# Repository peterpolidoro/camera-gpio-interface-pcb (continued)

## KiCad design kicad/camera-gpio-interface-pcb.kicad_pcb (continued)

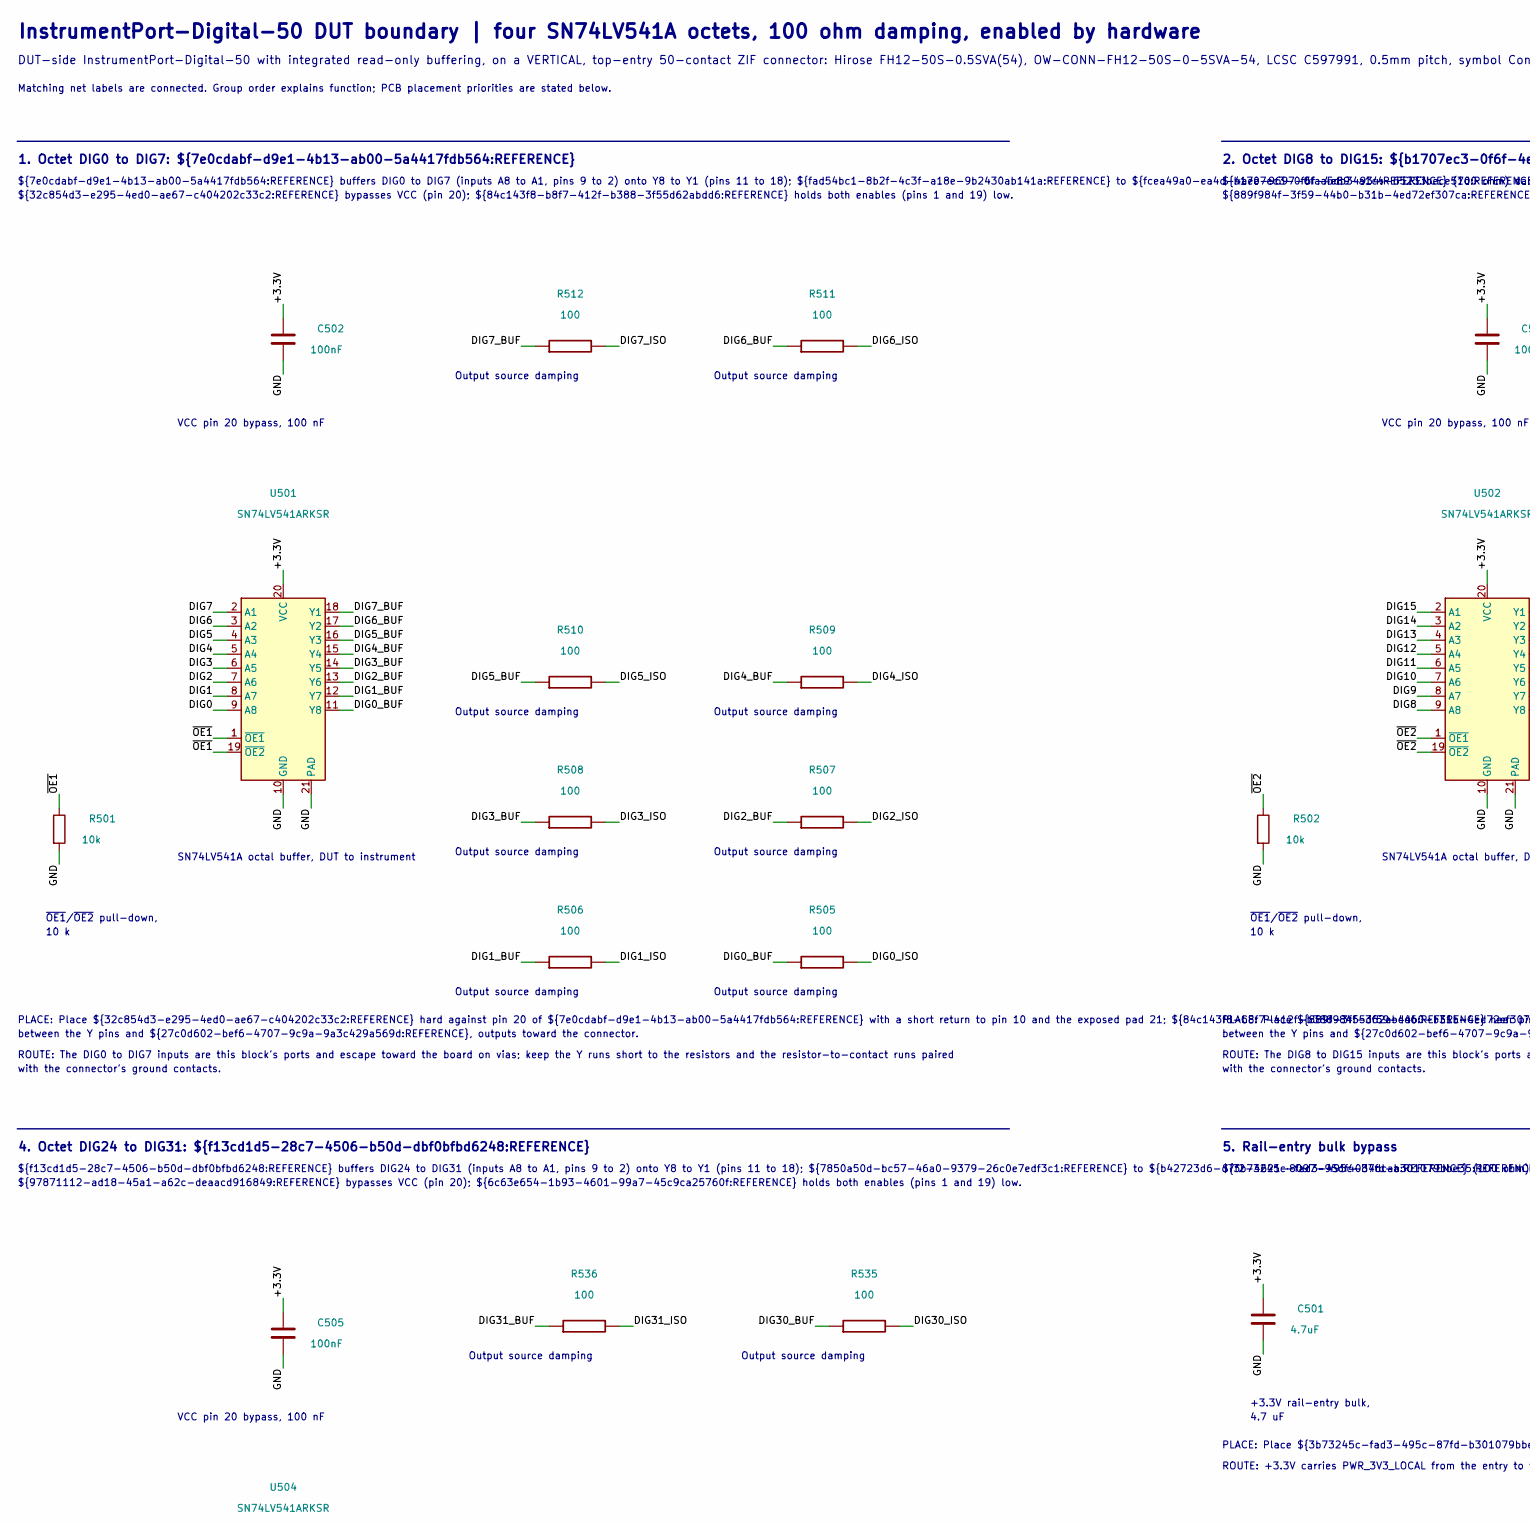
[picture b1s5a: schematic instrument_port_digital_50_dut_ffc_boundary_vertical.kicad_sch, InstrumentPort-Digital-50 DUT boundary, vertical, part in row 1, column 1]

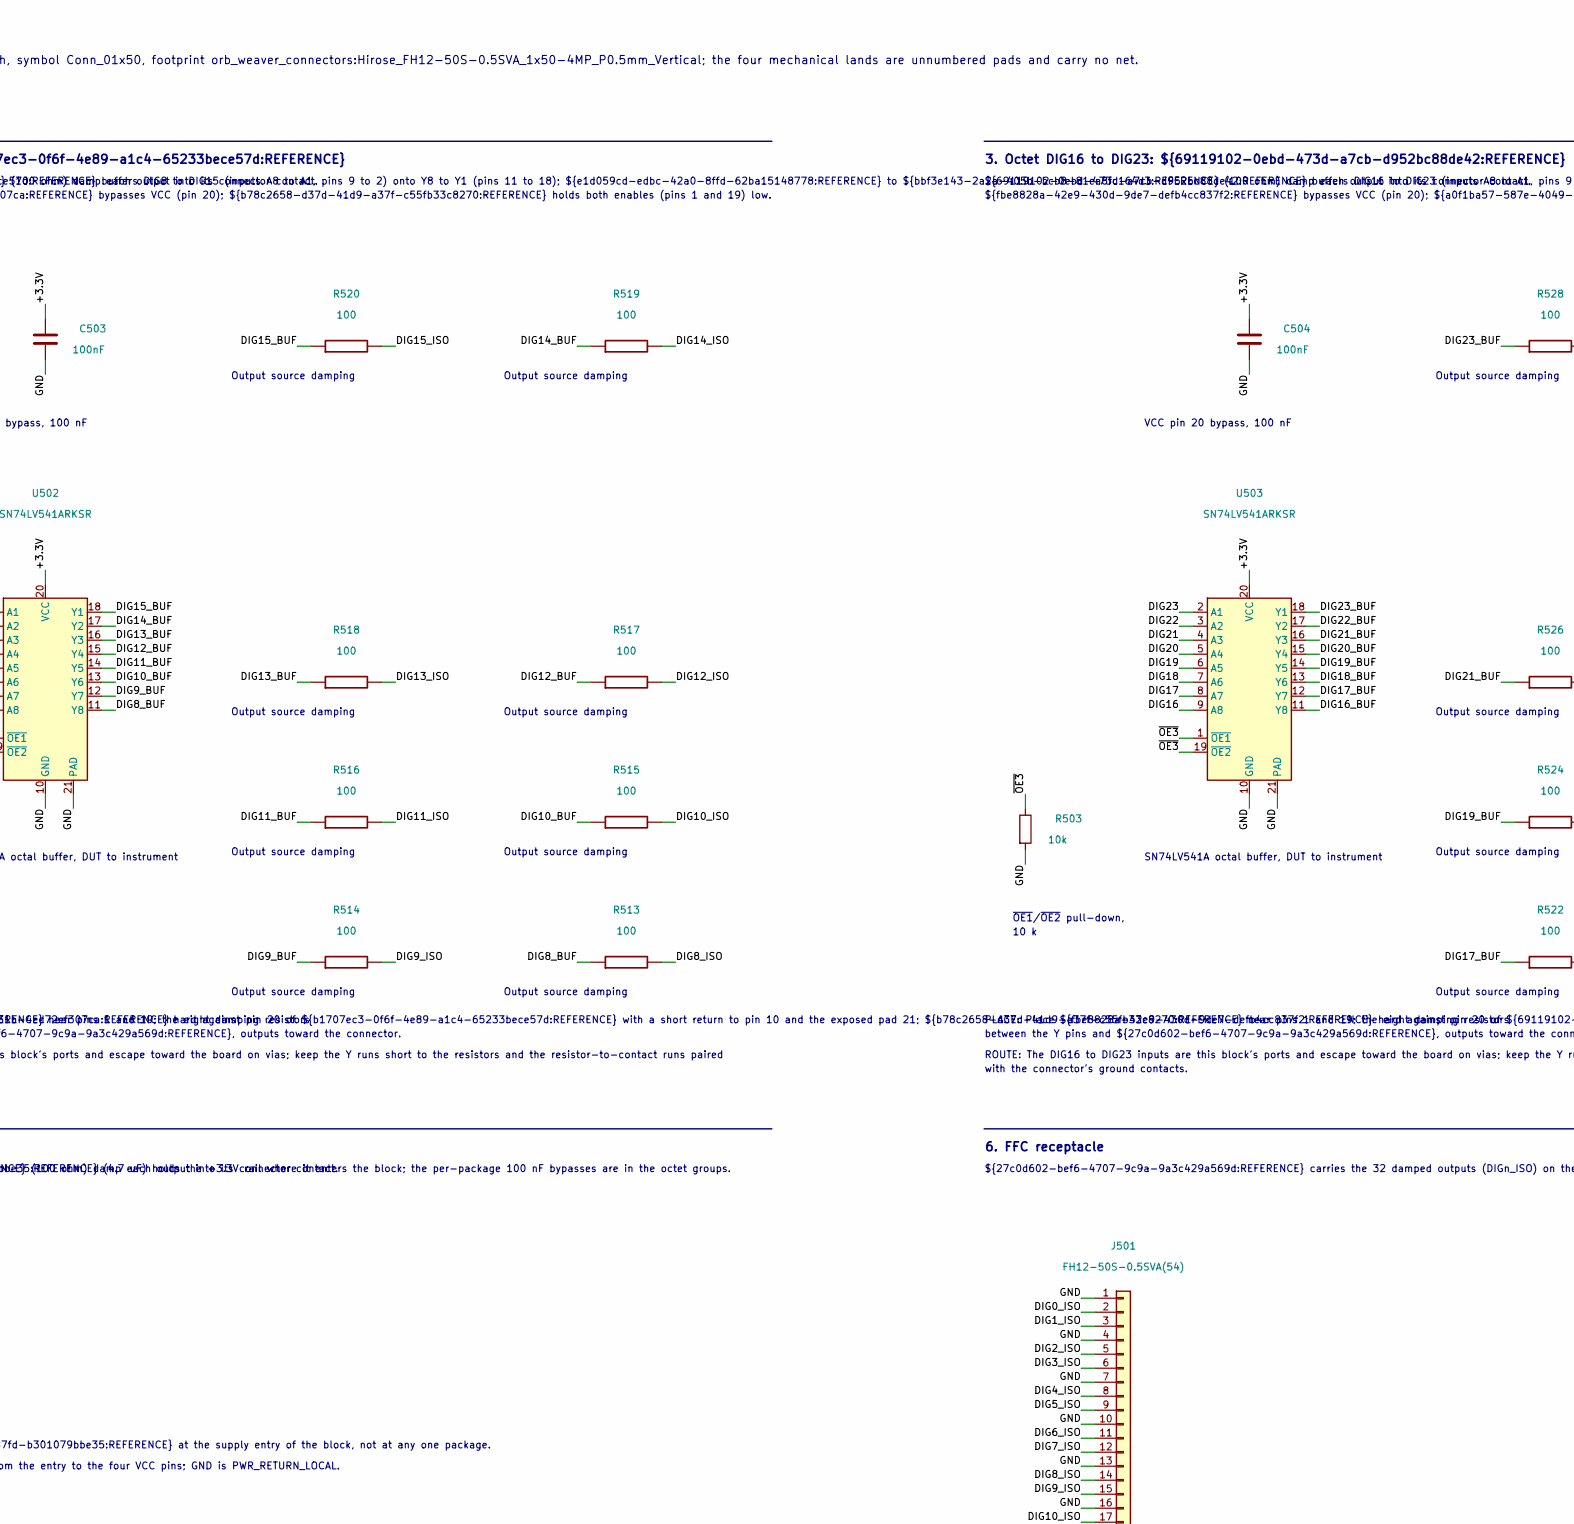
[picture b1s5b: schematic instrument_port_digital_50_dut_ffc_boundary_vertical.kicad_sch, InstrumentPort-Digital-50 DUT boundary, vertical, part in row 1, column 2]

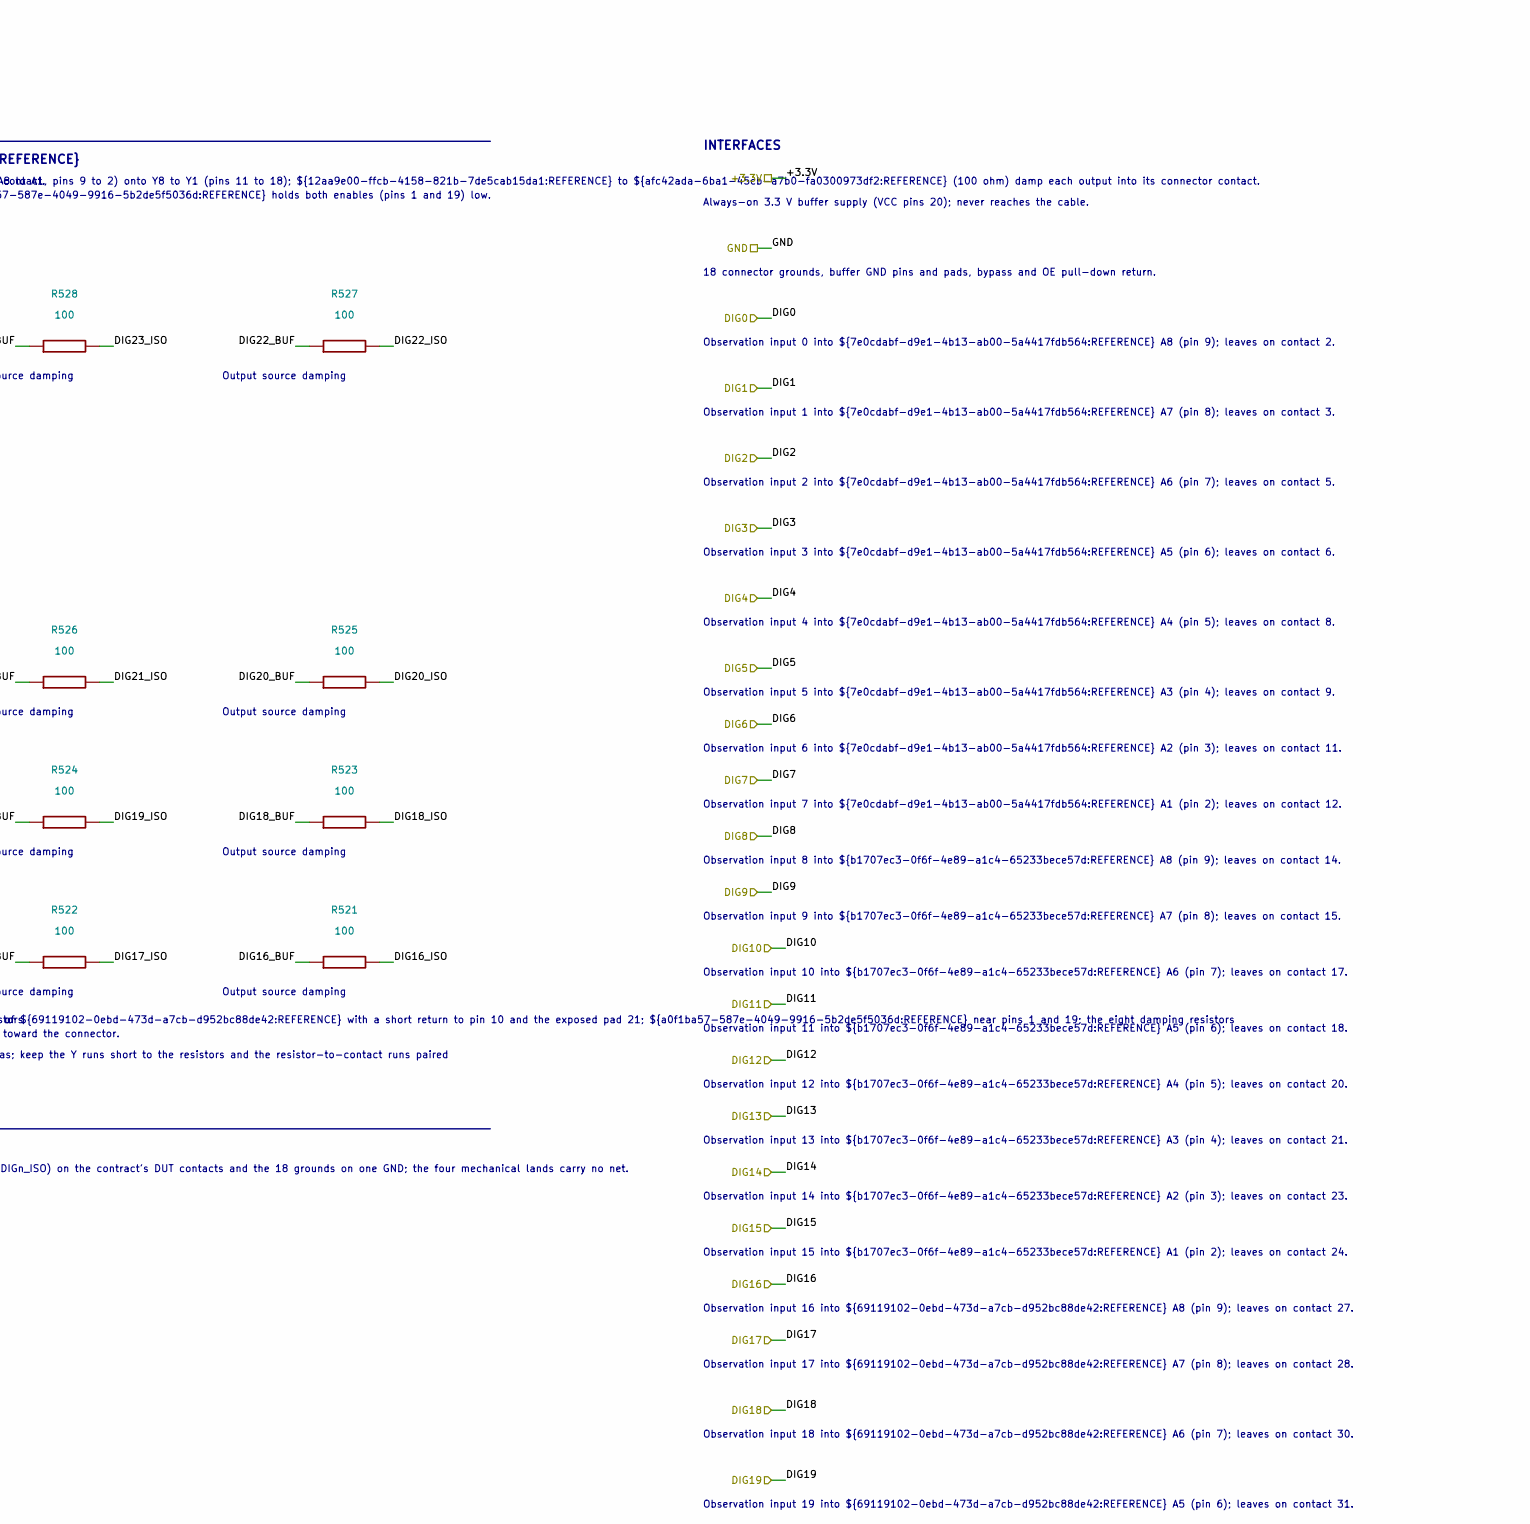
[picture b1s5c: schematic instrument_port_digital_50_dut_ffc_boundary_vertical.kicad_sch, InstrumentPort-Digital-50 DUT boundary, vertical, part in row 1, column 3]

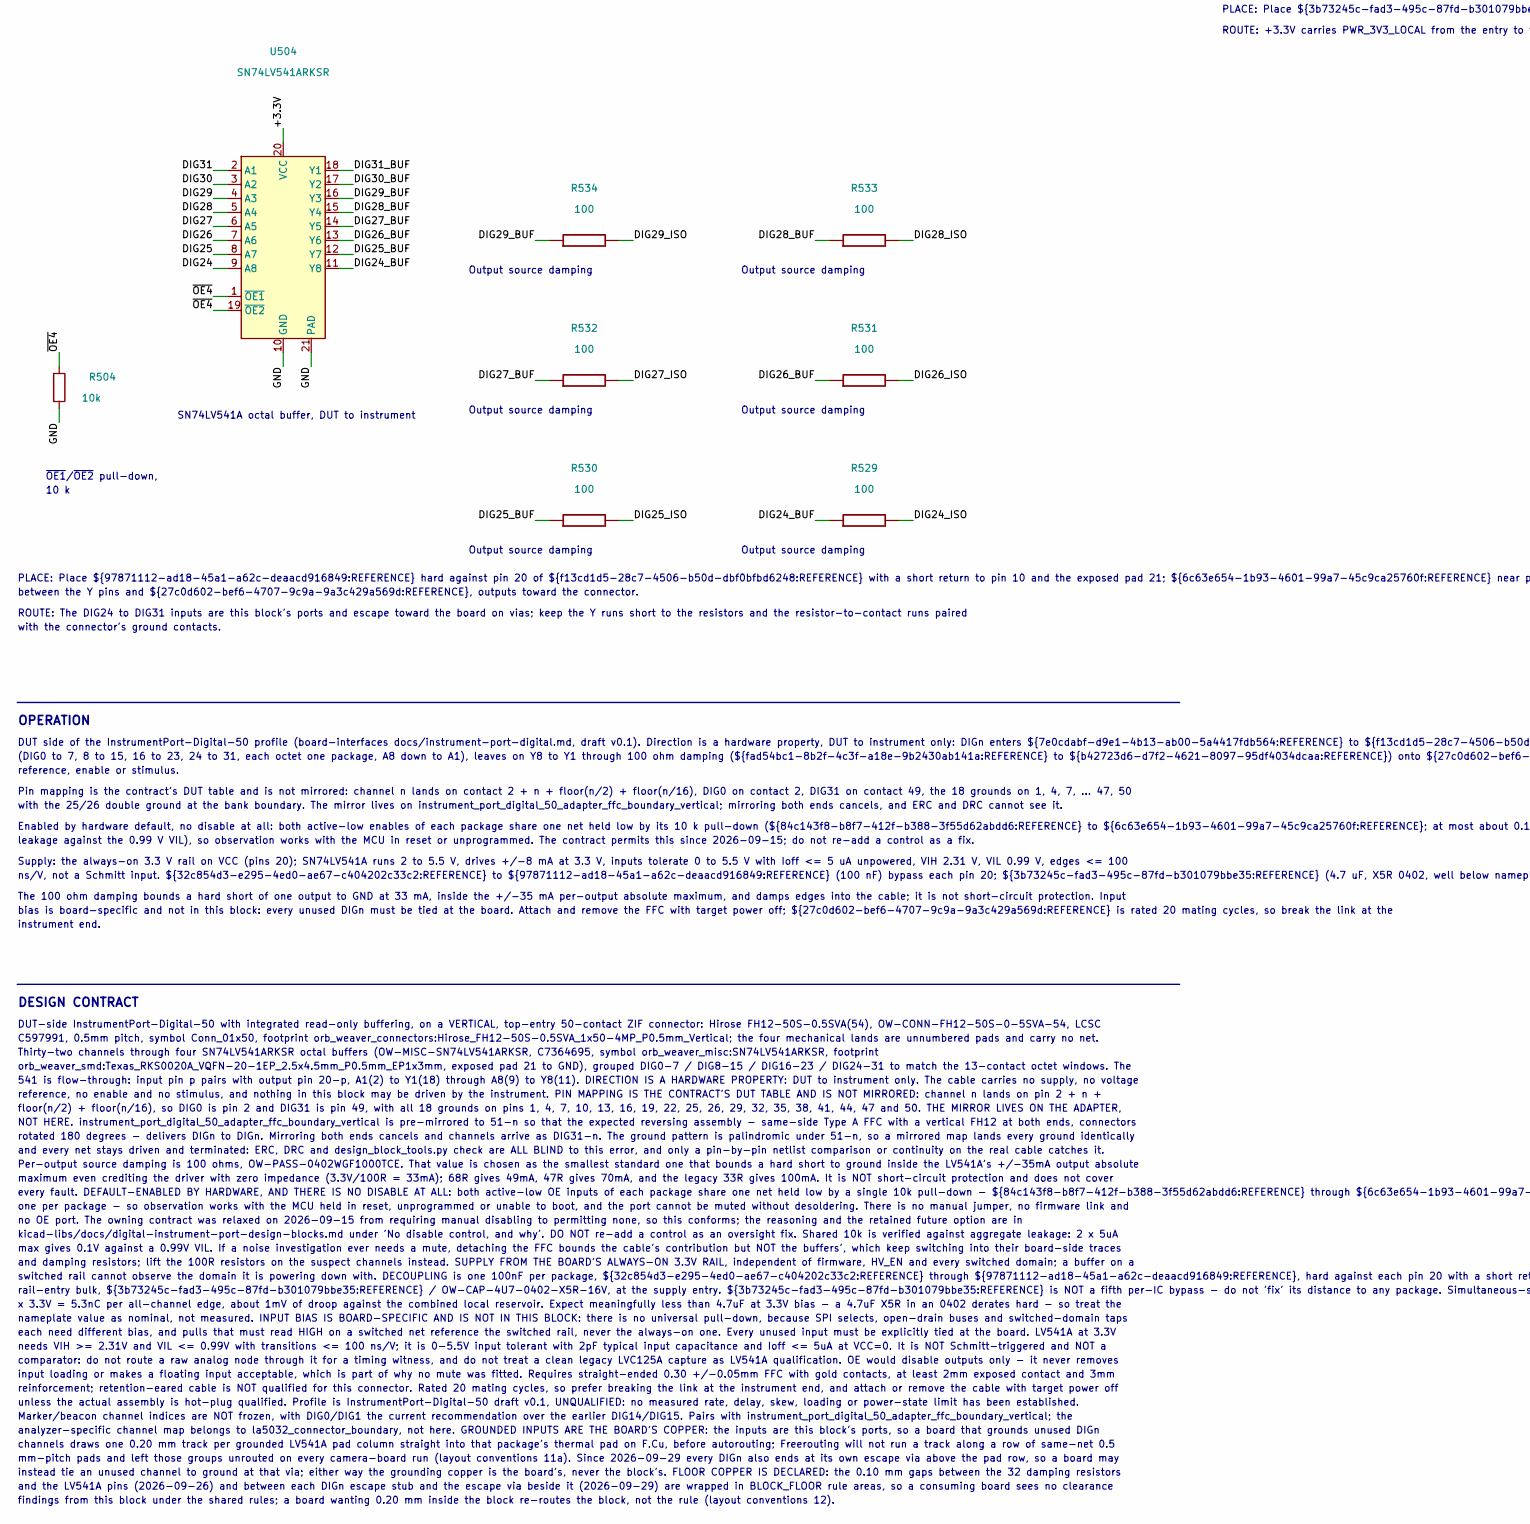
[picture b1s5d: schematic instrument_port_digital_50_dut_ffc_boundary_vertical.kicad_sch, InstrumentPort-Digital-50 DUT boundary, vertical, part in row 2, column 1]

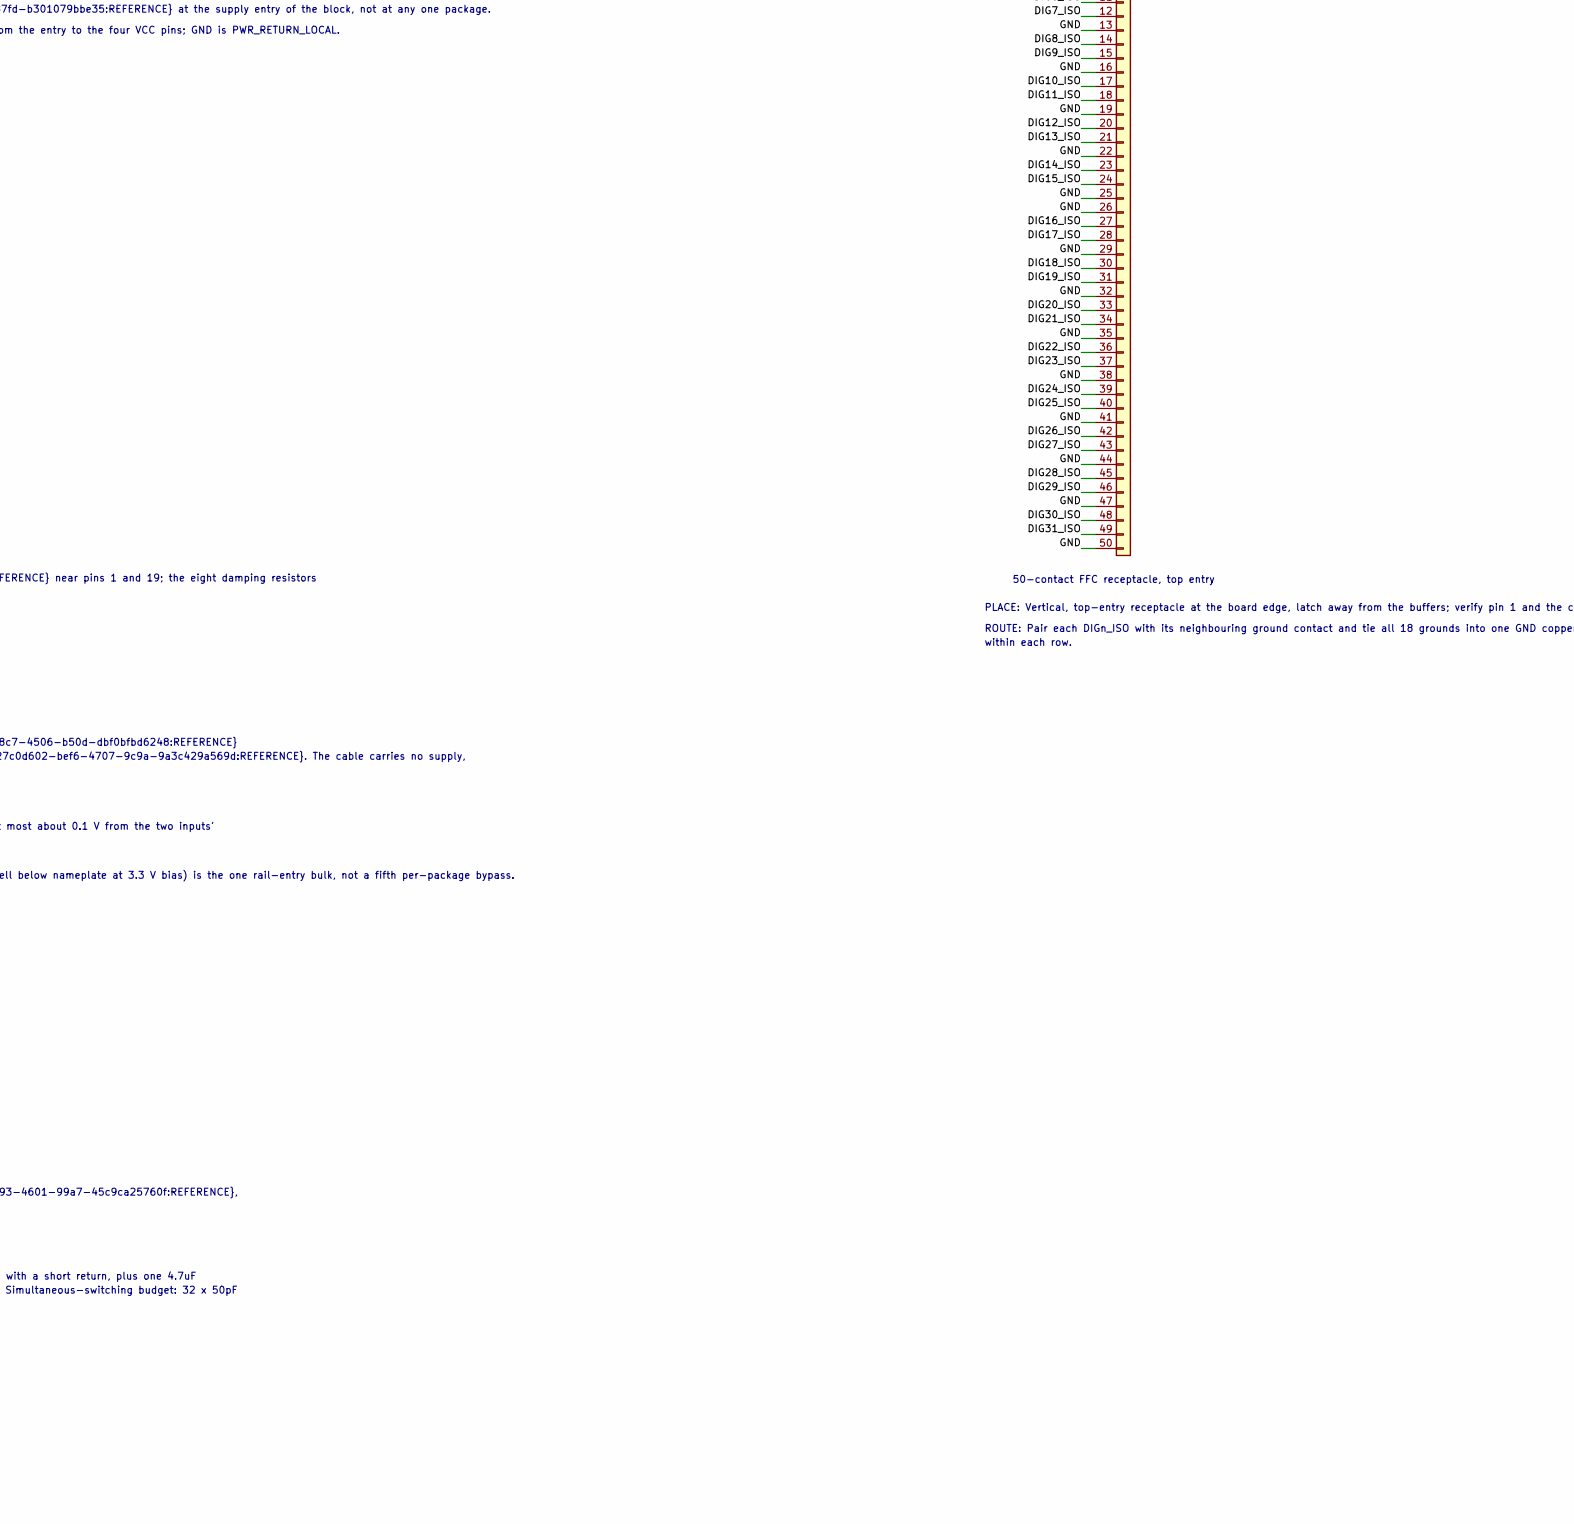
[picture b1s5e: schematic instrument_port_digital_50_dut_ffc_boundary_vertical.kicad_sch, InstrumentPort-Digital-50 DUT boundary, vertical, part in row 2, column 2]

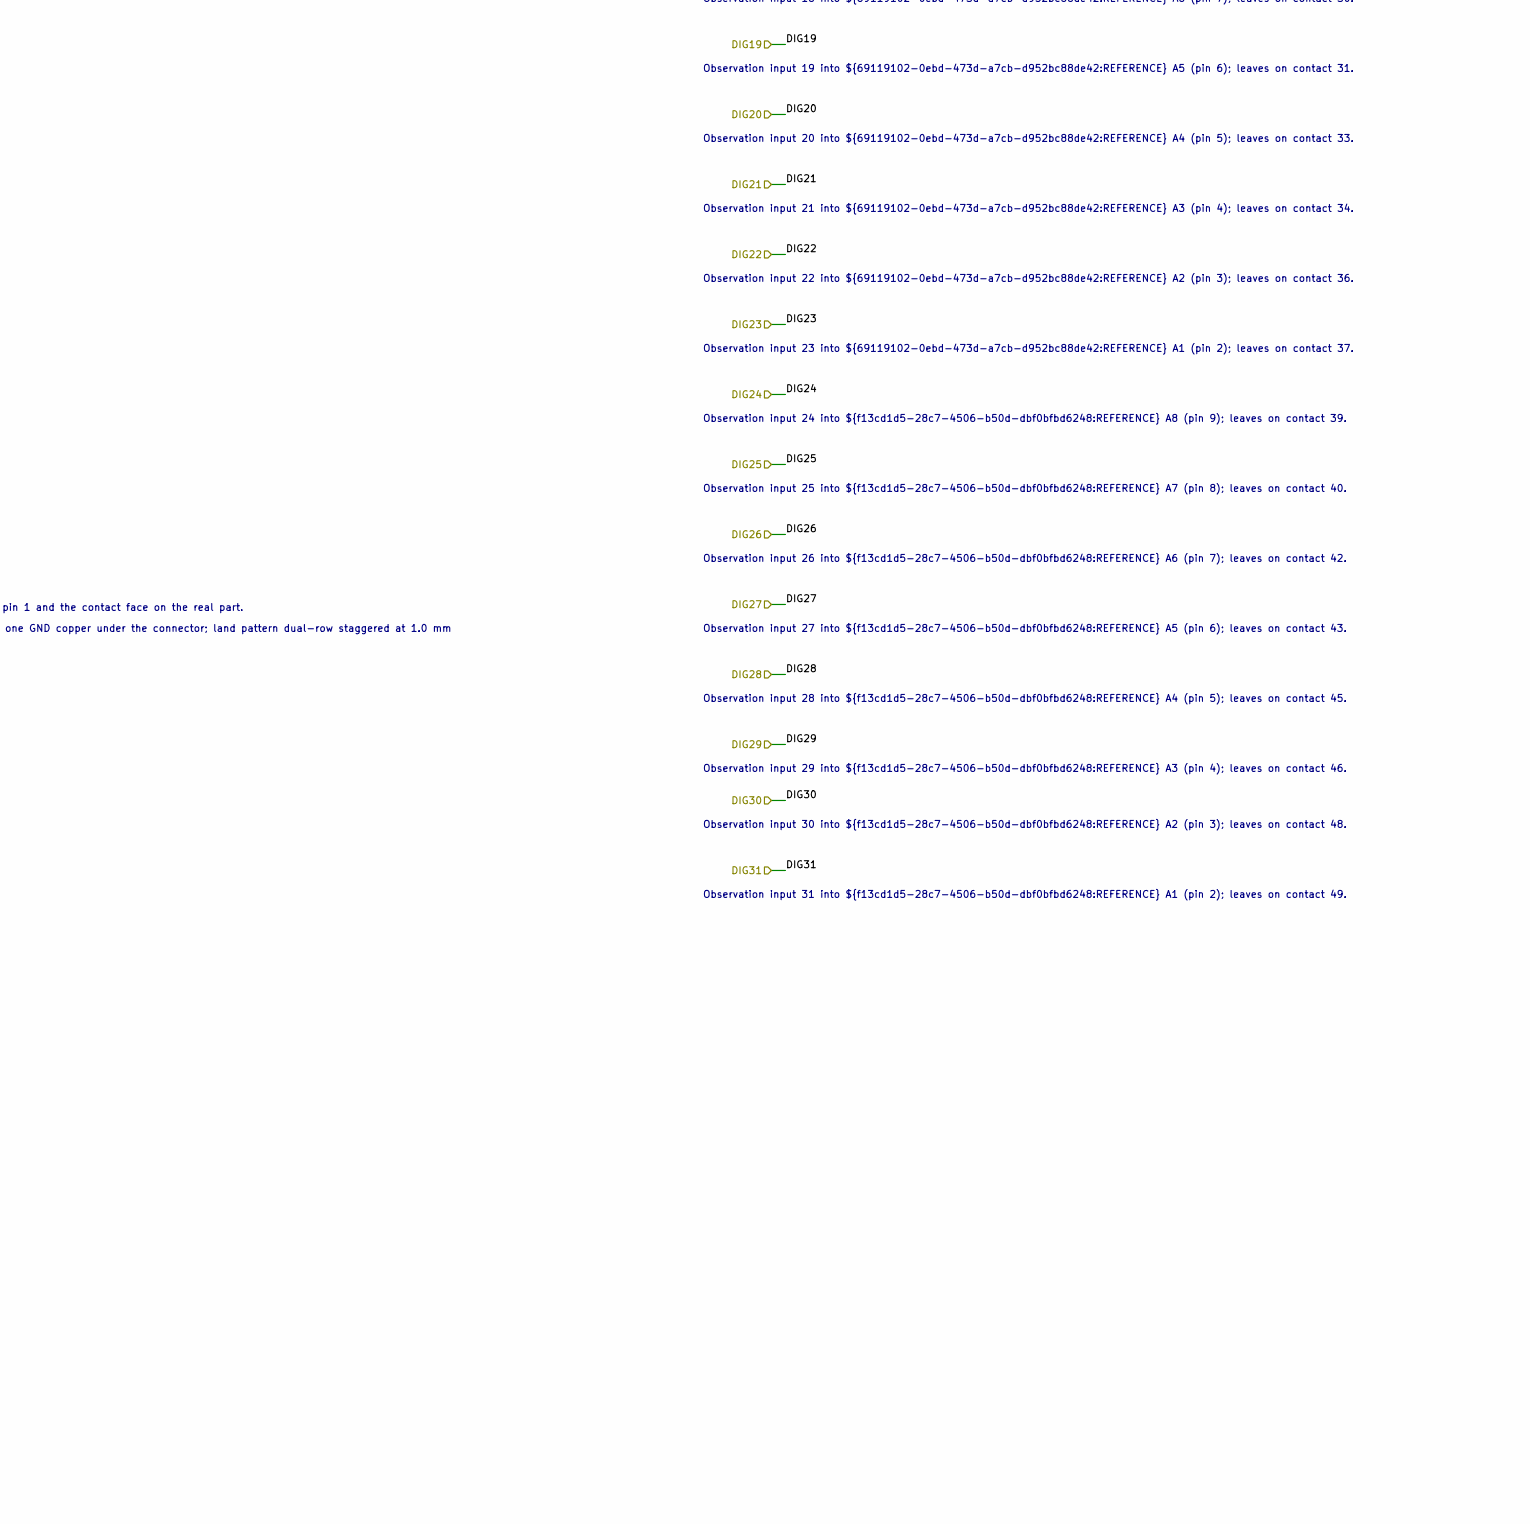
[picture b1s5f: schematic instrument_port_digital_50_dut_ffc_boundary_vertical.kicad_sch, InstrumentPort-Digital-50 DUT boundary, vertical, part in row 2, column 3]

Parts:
C501: 4.7uF; C_0402_1005Metric; PartID sym_orb_weaver_passives_c_4_7uf_25v_0402
C502, C503, C504, C505: 100nF; C_0402_1005Metric; PartID sym_orb_weaver_passives_c_0_1uf_100v_04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
J501: FH12-50S-0.5SVA(54); Hirose_FH12-50S-0.5SVA_1x50-4MP_P0.5mm_Vertical; PartID mpn_fh12_50s_0_5sva_54
R501, R502, R503, R504: 10k; R_0402_1005Metric; PartID sym_orb_weaver_passives_r_10_0k_0402
R505, R506, R507, R508, R509, R510, R511, R512, R513, R514, R515, R516, R517, R518, R519, R520, R521, R522, R523, R524, R525, R526, R527, R528, R529, R530, R531, R532, R533, R534, R535, R536: 100; R_0402_1005Metric; PartID sym_orb_weaver_passives_r_100_0402
U501, U502, U503, U504: SN74LV541ARKSR; Texas_RKS0020A_VQFN-20-1EP_2.5x4.5mm_P0.5mm_EP1x3mm; PartID sym_orb_weaver_misc_sn74lv541arksr

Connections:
/+3.3V: C501.1, C502.1, C503.1, C504.1, C505.1, U501.20 (VCC), U502.20 (VCC), U503.20 (VCC), U504.20 (VCC); also elsewhere on the board
/CAM1_L0_INST: U501.6 (A5); also elsewhere on the board
/CAM1_L1_INST: U501.5 (A4); also elsewhere on the board
/CAM1_L2_INST: U501.4 (A3); also elsewhere on the board
/CAM1_L3_INST: U501.3 (A2); also elsewhere on the board
/CAM1_OUT_INST: U501.2 (A1); also elsewhere on the board
/CAM2_L0_INST: U502.9 (A8); also elsewhere on the board
/CAM2_L1_INST: U502.8 (A7); also elsewhere on the board
/CAM2_L2_INST: U502.7 (A6); also elsewhere on the board
/CAM2_L3_INST: U502.6 (A5); also elsewhere on the board
/CAM2_OUT_INST: U502.5 (A4); also elsewhere on the board
/CAM3_L0_INST: U502.4 (A3); also elsewhere on the board
/CAM3_L1_INST: U502.3 (A2); also elsewhere on the board
/CAM3_L2_INST: U502.2 (A1); also elsewhere on the board
/CAM3_L3_INST: U503.9 (A8); also elsewhere on the board
/CAM3_OUT_INST: U503.8 (A7); also elsewhere on the board
/GND: C501.2, C502.2, C503.2, C504.2, C505.2, J501.1, J501.4, J501.7, J501.10, J501.13, J501.16, J501.19, J501.22, J501.25, J501.26, J501.29, J501.32, J501.35, J501.38, J501.41, J501.44, J501.47, J501.50, R501.2, R502.2, R503.2, R504.2, U501.10 (GND), U501.21 (PAD), U502.10 (GND), U502.21 (PAD), U503.2 (A1), U503.3 (A2), U503.4 (A3), U503.5 (A4), U503.6 (A5), U503.7 (A6), U503.10 (GND), U503.21 (PAD), U504.2 (A1), U504.3 (A2), U504.4 (A3), U504.5 (A4), U504.6 (A5), U504.7 (A6), U504.8 (A7), U504.9 (A8), U504.10 (GND), U504.21 (PAD); also elsewhere on the board
/SYNC_IN_INST: U501.8 (A7); also elsewhere on the board
/SYNC_OUT_INST: U501.7 (A6); also elsewhere on the board
/TRIG_IN_INST: U501.9 (A8); also elsewhere on the board
/instrument_port_digital_50_dut_ffc_boundary_vertical/DIG0_BUF: R505.1, U501.11 (Y8)
/instrument_port_digital_50_dut_ffc_boundary_vertical/DIG0_ISO: J501.2, R505.2
/instrument_port_digital_50_dut_ffc_boundary_vertical/DIG1_BUF: R506.1, U501.12 (Y7)
/instrument_port_digital_50_dut_ffc_boundary_vertical/DIG1_ISO: J501.3, R506.2
/instrument_port_digital_50_dut_ffc_boundary_vertical/DIG2_BUF: R507.1, U501.13 (Y6)
/instrument_port_digital_50_dut_ffc_boundary_vertical/DIG2_ISO: J501.5, R507.2
/instrument_port_digital_50_dut_ffc_boundary_vertical/DIG3_BUF: R508.1, U501.14 (Y5)
/instrument_port_digital_50_dut_ffc_boundary_vertical/DIG3_ISO: J501.6, R508.2
/instrument_port_digital_50_dut_ffc_boundary_vertical/DIG4_BUF: R509.1, U501.15 (Y4)
/instrument_port_digital_50_dut_ffc_boundary_vertical/DIG4_ISO: J501.8, R509.2
/instrument_port_digital_50_dut_ffc_boundary_vertical/DIG5_BUF: R510.1, U501.16 (Y3)
/instrument_port_digital_50_dut_ffc_boundary_vertical/DIG5_ISO: J501.9, R510.2
/instrument_port_digital_50_dut_ffc_boundary_vertical/DIG6_BUF: R511.1, U501.17 (Y2)
/instrument_port_digital_50_dut_ffc_boundary_vertical/DIG6_ISO: J501.11, R511.2
/instrument_port_digital_50_dut_ffc_boundary_vertical/DIG7_BUF: R512.1, U501.18 (Y1)
/instrument_port_digital_50_dut_ffc_boundary_vertical/DIG7_ISO: J501.12, R512.2
/instrument_port_digital_50_dut_ffc_boundary_vertical/DIG8_BUF: R513.1, U502.11 (Y8)
/instrument_port_digital_50_dut_ffc_boundary_vertical/DIG8_ISO: J501.14, R513.2
/instrument_port_digital_50_dut_ffc_boundary_vertical/DIG9_BUF: R514.1, U502.12 (Y7)
/instrument_port_digital_50_dut_ffc_boundary_vertical/DIG9_ISO: J501.15, R514.2
/instrument_port_digital_50_dut_ffc_boundary_vertical/DIG10_BUF: R515.1, U502.13 (Y6)
/instrument_port_digital_50_dut_ffc_boundary_vertical/DIG10_ISO: J501.17, R515.2
/instrument_port_digital_50_dut_ffc_boundary_vertical/DIG11_BUF: R516.1, U502.14 (Y5)
/instrument_port_digital_50_dut_ffc_boundary_vertical/DIG11_ISO: J501.18, R516.2
/instrument_port_digital_50_dut_ffc_boundary_vertical/DIG12_BUF: R517.1, U502.15 (Y4)
/instrument_port_digital_50_dut_ffc_boundary_vertical/DIG12_ISO: J501.20, R517.2
/instrument_port_digital_50_dut_ffc_boundary_vertical/DIG13_BUF: R518.1, U502.16 (Y3)
/instrument_port_digital_50_dut_ffc_boundary_vertical/DIG13_ISO: J501.21, R518.2
/instrument_port_digital_50_dut_ffc_boundary_vertical/DIG14_BUF: R519.1, U502.17 (Y2)
/instrument_port_digital_50_dut_ffc_boundary_vertical/DIG14_ISO: J501.23, R519.2
/instrument_port_digital_50_dut_ffc_boundary_vertical/DIG15_BUF: R520.1, U502.18 (Y1)
/instrument_port_digital_50_dut_ffc_boundary_vertical/DIG15_ISO: J501.24, R520.2
/instrument_port_digital_50_dut_ffc_boundary_vertical/DIG16_BUF: R521.1, U503.11 (Y8)
/instrument_port_digital_50_dut_ffc_boundary_vertical/DIG16_ISO: J501.27, R521.2
/instrument_port_digital_50_dut_ffc_boundary_vertical/DIG17_BUF: R522.1, U503.12 (Y7)
/instrument_port_digital_50_dut_ffc_boundary_vertical/DIG17_ISO: J501.28, R522.2
/instrument_port_digital_50_dut_ffc_boundary_vertical/DIG18_BUF: R523.1, U503.13 (Y6)
/instrument_port_digital_50_dut_ffc_boundary_vertical/DIG18_ISO: J501.30, R523.2
/instrument_port_digital_50_dut_ffc_boundary_vertical/DIG19_BUF: R524.1, U503.14 (Y5)
/instrument_port_digital_50_dut_ffc_boundary_vertical/DIG19_ISO: J501.31, R524.2
/instrument_port_digital_50_dut_ffc_boundary_vertical/DIG20_BUF: R525.1, U503.15 (Y4)
/instrument_port_digital_50_dut_ffc_boundary_vertical/DIG20_ISO: J501.33, R525.2
/instrument_port_digital_50_dut_ffc_boundary_vertical/DIG21_BUF: R526.1, U503.16 (Y3)
/instrument_port_digital_50_dut_ffc_boundary_vertical/DIG21_ISO: J501.34, R526.2
/instrument_port_digital_50_dut_ffc_boundary_vertical/DIG22_BUF: R527.1, U503.17 (Y2)
/instrument_port_digital_50_dut_ffc_boundary_vertical/DIG22_ISO: J501.36, R527.2
/instrument_port_digital_50_dut_ffc_boundary_vertical/DIG23_BUF: R528.1, U503.18 (Y1)
/instrument_port_digital_50_dut_ffc_boundary_vertical/DIG23_ISO: J501.37, R528.2
/instrument_port_digital_50_dut_ffc_boundary_vertical/DIG24_BUF: R529.1, U504.11 (Y8)
/instrument_port_digital_50_dut_ffc_boundary_vertical/DIG24_ISO: J501.39, R529.2
/instrument_port_digital_50_dut_ffc_boundary_vertical/DIG25_BUF: R530.1, U504.12 (Y7)
/instrument_port_digital_50_dut_ffc_boundary_vertical/DIG25_ISO: J501.40, R530.2
/instrument_port_digital_50_dut_ffc_boundary_vertical/DIG26_BUF: R531.1, U504.13 (Y6)
/instrument_port_digital_50_dut_ffc_boundary_vertical/DIG26_ISO: J501.42, R531.2
/instrument_port_digital_50_dut_ffc_boundary_vertical/DIG27_BUF: R532.1, U504.14 (Y5)
/instrument_port_digital_50_dut_ffc_boundary_vertical/DIG27_ISO: J501.43, R532.2
/instrument_port_digital_50_dut_ffc_boundary_vertical/DIG28_BUF: R533.1, U504.15 (Y4)
/instrument_port_digital_50_dut_ffc_boundary_vertical/DIG28_ISO: J501.45, R533.2
/instrument_port_digital_50_dut_ffc_boundary_vertical/DIG29_BUF: R534.1, U504.16 (Y3)
/instrument_port_digital_50_dut_ffc_boundary_vertical/DIG29_ISO: J501.46, R534.2
/instrument_port_digital_50_dut_ffc_boundary_vertical/DIG30_BUF: R535.1, U504.17 (Y2)
/instrument_port_digital_50_dut_ffc_boundary_vertical/DIG30_ISO: J501.48, R535.2
/instrument_port_digital_50_dut_ffc_boundary_vertical/DIG31_BUF: R536.1, U504.18 (Y1)
/instrument_port_digital_50_dut_ffc_boundary_vertical/DIG31_ISO: J501.49, R536.2
/instrument_port_digital_50_dut_ffc_boundary_vertical/~OE1: R501.1, U501.1 (~OE1), U501.19 (~OE2)
/instrument_port_digital_50_dut_ffc_boundary_vertical/~OE2: R502.1, U502.1 (~OE1), U502.19 (~OE2)
/instrument_port_digital_50_dut_ffc_boundary_vertical/~OE3: R503.1, U503.1 (~OE1), U503.19 (~OE2)
/instrument_port_digital_50_dut_ffc_boundary_vertical/~OE4: R504.1, U504.1 (~OE1), U504.19 (~OE2)

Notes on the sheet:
InstrumentPort-Digital-50 DUT boundary | four SN74LV541A octets, 100 ohm damping, enabled by hardware
DUT-side InstrumentPort-Digital-50 with integrated read-only buffering, on a VERTICAL, top-entry 50-contact ZIF connector: Hirose FH12-50S-0.5SVA(54), OW-CONN-FH12-50S-0-5SVA-54, LCSC C597991, 0.5mm pitch, symbol Conn_01x50, footprint orb_weaver_connectors:Hirose_FH12-50S-0.5SVA_1x50-4MP_P0.5mm_Ver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
Matching net labels are connected. Group order explains function; PCB placement priorities are stated below.
1. Octet DIG0 to DIG7: ${7e0cdabf-d9e1-4b13-ab00-5a4417fdb564:REFERENCE}
${7e0cdabf-d9e1-4b13-ab00-5a4417fdb564:REFERENCE} buffers DIG0 to DIG7 (inputs A8 to A1, pins 9 to 2) onto Y8 to Y1 (pins 11 to 18); ${fad54bc1-8b2f-4c3f-a18e-9b2430ab141a:REFERENCE} to ${fcea49a0-ea4d-4aee-9697-0faa5db34934:REFERENCE} (100 ohm) damp each output into its connector contact.
${32c854d3-e295-4ed0-ae67-c404202c33c2:REFERENCE} bypasses VCC (pin 20); ${84c143f8-b8f7-412f-b388-3f55d62abdd6:REFERENCE} holds both enables (pins 1 and 19) low.
VCC pin 20 bypass, 100 nF
Output source damping
SN74LV541A octal buffer, DUT to instrument
~{OE1}/~{OE2} pull-down,
10 k
PLACE: Place ${32c854d3-e295-4ed0-ae67-c404202c33c2:REFERENCE} hard against pin 20 of ${7e0cdabf-d9e1-4b13-ab00-5a4417fdb564:REFERENCE} with a short return to pin 10 and the exposed pad 21; ${84c143f8-b8f7-412f-b388-3f55d62abdd6:REFERENCE} near pins 1 and 19; the eight damping resistors
between the Y pins and ${27c0d602-bef6-4707-9c9a-9a3c429a569d:REFERENCE}, outputs toward the connector.
ROUTE: The DIG0 to DIG7 inputs are this block's ports and escape toward the board on vias; keep the Y runs short to the resistors and the resistor-to-contact runs paired
with the connector's ground contacts.
2. Octet DIG8 to DIG15: ${b1707ec3-0f6f-4e89-a1c4-65233bece57d:REFERENCE}
${b1707ec3-0f6f-4e89-a1c4-65233bece57d:REFERENCE} buffers DIG8 to DIG15 (inputs A8 to A1, pins 9 to 2) onto Y8 to Y1 (pins 11 to 18); ${e1d059cd-edbc-42a0-8ffd-62ba15148778:REFERENCE} to ${bbf3e143-2a2a-405b-bcb8-81ea8fc164d3:REFERENCE} (100 ohm) damp each output into its connector contact.
${889f984f-3f59-44b0-b31b-4ed72ef307ca:REFERENCE} bypasses VCC (pin 20); ${b78c2658-d37d-41d9-a37f-c55fb33c8270:REFERENCE} holds both enables (pins 1 and 19) low.
PLACE: Place ${889f984f-3f59-44b0-b31b-4ed72ef307ca:REFERENCE} hard against pin 20 of ${b1707ec3-0f6f-4e89-a1c4-65233bece57d:REFERENCE} with a short return to pin 10 and the exposed pad 21; ${b78c2658-d37d-41d9-a37f-c55fb33c8270:REFERENCE} near pins 1 and 19; the eight damping resistors
ROUTE: The DIG8 to DIG15 inputs are this block's ports and escape toward the board on vias; keep the Y runs short to the resistors and the resistor-to-contact runs paired
3. Octet DIG16 to DIG23: ${69119102-0ebd-473d-a7cb-d952bc88de42:REFERENCE}
${69119102-0ebd-473d-a7cb-d952bc88de42:REFERENCE} buffers DIG16 to DIG23 (inputs A8 to A1, pins 9 to 2) onto Y8 to Y1 (pins 11 to 18); ${12aa9e00-ffcb-4158-821b-7de5cab15da1:REFERENCE} to ${afc42ada-6ba1-45cb-a7b0-fa0300973df2:REFERENCE} (100 ohm) damp each output into its connector contact.
${fbe8828a-42e9-430d-9de7-defb4cc837f2:REFERENCE} bypasses VCC (pin 20); ${a0f1ba57-587e-4049-9916-5b2de5f5036d:REFERENCE} holds both enables (pins 1 and 19) low.
PLACE: Place ${fbe8828a-42e9-430d-9de7-defb4cc837f2:REFERENCE} hard against pin 20 of ${69119102-0ebd-473d-a7cb-d952bc88de42:REFERENCE} with a short return to pin 10 and the exposed pad 21; ${a0f1ba57-587e-4049-9916-5b2de5f5036d:REFERENCE} near pins 1 and 19; the eight damping resistors
ROUTE: The DIG16 to DIG23 inputs are this block's ports and escape toward the board on vias; keep the Y runs short to the resistors and the resistor-to-contact runs paired
4. Octet DIG24 to DIG31: ${f13cd1d5-28c7-4506-b50d-dbf0bfbd6248:REFERENCE}
${f13cd1d5-28c7-4506-b50d-dbf0bfbd6248:REFERENCE} buffers DIG24 to DIG31 (inputs A8 to A1, pins 9 to 2) onto Y8 to Y1 (pins 11 to 18); ${7850a50d-bc57-46a0-9379-26c0e7edf3c1:REFERENCE} to ${b42723d6-d7f2-4621-8097-95df4034dcaa:REFERENCE} (100 ohm) damp each output into its connector contact.
${97871112-ad18-45a1-a62c-deaacd916849:REFERENCE} bypasses VCC (pin 20); ${6c63e654-1b93-4601-99a7-45c9ca25760f:REFERENCE} holds both enables (pins 1 and 19) low.
PLACE: Place ${97871112-ad18-45a1-a62c-deaacd916849:REFERENCE} hard against pin 20 of ${f13cd1d5-28c7-4506-b50d-dbf0bfbd6248:REFERENCE} with a short return to pin 10 and the exposed pad 21; ${6c63e654-1b93-4601-99a7-45c9ca25760f:REFERENCE} near pins 1 and 19; the eight damping resistors
ROUTE: The DIG24 to DIG31 inputs are this block's ports and escape toward the board on vias; keep the Y runs short to the resistors and the resistor-to-contact runs paired
5. Rail-entry bulk bypass
${3b73245c-fad3-495c-87fd-b301079bbe35:REFERENCE} (4.7 uF) holds the +3.3V rail where it enters the block; the per-package 100 nF bypasses are in the octet groups.
+3.3V rail-entry bulk,
4.7 uF
PLACE: Place ${3b73245c-fad3-495c-87fd-b301079bbe35:REFERENCE} at the supply entry of the block, not at any one package.
ROUTE: +3.3V carries PWR_3V3_LOCAL from the entry to the four VCC pins; GND is PWR_RETURN_LOCAL.
6. FFC receptacle
${27c0d602-bef6-4707-9c9a-9a3c429a569d:REFERENCE} carries the 32 damped outputs (DIGn_ISO) on the contract's DUT contacts and the 18 grounds on one GND; the four mechanical lands carry no net.
50-contact FFC receptacle, top entry
PLACE: Vertical, top-entry receptacle at the board edge, latch away from the buffers; verify pin 1 and the contact face on the real part.
